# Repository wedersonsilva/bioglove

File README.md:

# Bioglove: Prototype of a bioinspired flexion transducer 
A project used in my undergraduate thesis [pt-br] 

# Abstract
Gloves embedded with sensors, also known as data gloves, allow interactions with virtual reality, robotics, control, internet of things, telemedicine, and so on. Essentially, such interaction occurs through the mapping of hands position as well as the flexion degree of the fingers for certain movements and actions within the environment in which the glove is submitted. The cost of the glove in many projects becomes prohibitive because of the technology chosen for such mapping. In the specific case of measuring the degree of flexion of the fingers — there are solutions based on fiber optics, conductive ink, resistive bending sensors and potentiometers. In order to reduce the cost of projects that require a data glove, was developed the BioGlove: a generic glove with low-cost embedded flexion sensors inspired by finger biomechanics. For the control and communication of the glove, a microcontroller board that has wide documentation and availability was used and a simplified protocol of communication and control was developed. The prototype developed was used for wireless control of an electronic car and its performance was compared with commercial solutions documented in the literature. The results showed that the BioGlove performs similarly to its competitors, especially in the flexion mapping and energy consumption requirements.

# Thesis
A .pdf version of the complete undergraduate thesis [pt-br] can be found .

# Note
This project was also known as Low Cost Flex Sensor (lcfs)

# Issues
Some archives are missing and they will be uploaded as soon as possible

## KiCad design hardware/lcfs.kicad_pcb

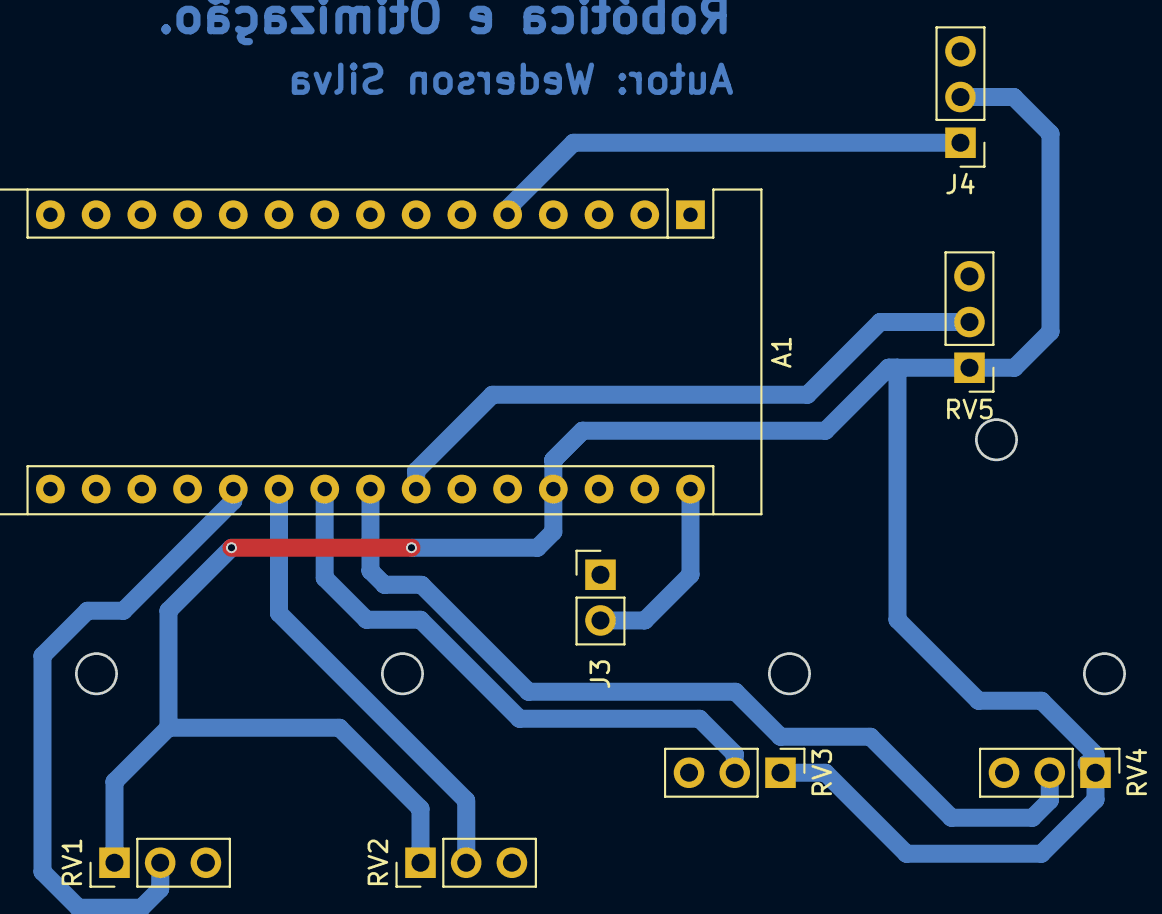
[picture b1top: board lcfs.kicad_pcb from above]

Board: 2 copper layers, 8 parts (0 on the bottom side), 9 nets.

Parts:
A1: Arduino_Nano
J3: Pin_1x2_Battery; Socket_Strip_Straight_1x02_Pitch2.54mm
J4: Pin_1x3_Transmissor; Socket_Strip_Straight_1x03_Pitch2.54mm
RV1: POT 1; Socket_Strip_Straight_1x03_Pitch2.54mm
RV2: POT 2; Socket_Strip_Straight_1x03_Pitch2.54mm
RV3: POT 3; Socket_Strip_Straight_1x03_Pitch2.54mm
RV4: POT 4; Socket_Strip_Straight_1x03_Pitch2.54mm
RV5: POT 5; Socket_Strip_Straight_1x03_Pitch2.54mm

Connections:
/5V: A1.27, J4.2, RV1.1, RV2.1, RV3.1, RV4.1, RV5.1
/7.2V: A1.30, J3.2
/DATA: A1.5, J4.1
/GND: A1.4, A1.29, J3.1, J4.3, RV1.3, RV2.3, RV3.3, RV4.3, RV5.3
unnamed: A1.20, RV1.2
unnamed: A1.21, RV2.2
unnamed: A1.22, RV3.2
unnamed: A1.23, RV4.2
unnamed: A1.24, RV5.2

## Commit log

2018-06-09 v.0.1.0 - Sending first archives
2018-06-09 v.0.1.1 - Sending first software test
2018-06-09 v0.1.2 - Ler cinco potenciomêtros e enviar ao Serial Monitor
2018-06-11 v0.1.3 - Incluir 2 softwares .ino para testar transmissão
2018-06-11 v0.1.4 - Segundo teste de transmissão de sinal concluído com sucesso
2018-06-13 v0.1.5 Remapeamento de valores lidos de 0-1023 para 1-8
2018-06-14 v0.1.6 Reorganiza e cria funcoes
2018-06-14 v0.1.7 Testa o envio de numeros variaveis
2018-06-14 v0.1.8 Inclui o projeto do Kicad
2018-06-15 v0.1.9 Inclui componentes no esquematico do Kicad
2018-06-16 v0.1.10 Esquemático finalizado e PCB iniciada
2018-06-19 v0.1.11 Inclui arquivos QCAD de desenho técnico
2018-06-19 v0.1.12 Posicionamento dos componentes na PCB
2018-06-19 v0.1.13 PCB organizada e não preenchida
2018-06-21 v0.1.14 PCB preenchida e inclusão da pasta pictures
2018-06-21 v0.1.15 Renomeia valores
2018-06-23 v0.1.16 Concatena e envia números variáveis
2018-06-23 Limpa (organiza) o código
2018-06-23 v0.1.18 Organiza e diminui o código ao mínimo
2018-06-24 v0.1.19 Coleta e envia valores variáveis para outro Arduino
2018-06-24 v0.1.20 <Bug> :bug: Apenas testa a mensagem de commit
2018-06-25 v0.1.21 :+1: Recebe, divide e transmite para 4 LEDs o código recebido
2018-06-30 v0.1.22 Envia e recebe 10 níveis de flexão
2018-07-01 v0.1.23 Inclui setup inicial do texto
2018-07-02 v0.2.2 Cria a estrutura básica do documento
2018-07-02 v0.2.3 Adiciona referências
2018-07-04 v0.2.4 Adiciona referências e o primeiro texto sobre Potenciômetro
2018-07-23 v0.2.5 Adiciona o SVG das mãos
2018-08-06 v0.2.6 Adiciona o SVG sobre potenciômetros
2018-08-06 v0.2.6 Adiciona a função de giro do potenciômetro
2018-08-07 v0.2.7 Compila todo o lcfs.tex após a última atualização
2018-08-07 v0.2.8 Adiciona texto ao trecho 'Movimentação dos Dedos'
2018-08-07 v0.2.9 Adiciona o movimento dos tendões na mão
2018-11-19 Adiciona fotos ao cap. 2 e texto ao cap. 3
2018-11-20 Adiciona desenhos ao cap. 3
2018-11-20 Inclui o desenho do receptor RF
2018-11-21 Inclui prints e fotos da PCB no Cap 3
2018-11-23 Conserta as referências e adapta o doc para o formato ABNT
2018-11-23 Deleta a pasta pictures e o arquivo .lcfs.tex.swp
2018-11-23 Compila o documento no formato ABNT
2018-11-24 Deleta e renomeia figuras
2018-11-25 Adiciona texto ao trecho 'Movimento Mecânico'
2018-11-26 Organiza e adiciona figuras no padrão ABNT ao cap. 3
2018-11-26 Reorganiza subcapítulos do cap. 3:w
2018-11-27 Adiciona a seção 'Montagem' ao Cap. 3
2018-11-27 Adiciona fotos melhores ao trabalho
2018-11-30 Adiciona correções baseadas no 1º feedback do orientador
2018-12-04 Adiciona primeiras correções e imagens baseadas no 2º feedback do orientador
2018-12-04 Adiciona mais correções baseadas no 2º feedback do orientador
2018-12-05 Adiciona textos e imagens sobre o protocolo de controle
2018-12-06 Adiciona a 1a versão após o 2º feedback do orientador
2018-12-06 Adiciona a 3a versão do Cap 3 após o 2º feedback do orientador
2018-12-13 Inclui novas referências para o Cap. 2
2018-12-15 Inclui ao Cap. 2 textos referenciados
2018-12-16 Adiciona o texto sobre microcontroladores
2018-12-18 Inclui a versão 3 do Cap. 2
2019-01-05 Inclui o início do Cap 4 e mais referências
2019-01-06 Inclui o trecho sobre baterias ao Cap. 4:w
2019-01-06 Conclui o trecho sobre baterias no Cap. 4
2019-01-07 Adiciona a versão 6 do TCC, com quase tudo mal finalizado
2019-02-18 Adiciona arquivos e testa funcionalidades do git
    As duas versões dos formulários (.doc e .pdf) usados na matrícula 2019.2 foram adicionadas ao
    projeto. Uma nova forma de commit, usando o editor nvim foi utilizada
    para escrever esse log.
2019-02-19 Inicia a correção baseado no 1º feedback de 2019
    Após receber o pdf com as marcações indicadas pelo orientador, foram
    iniciadas as correções baseadas nas marcações do último texto enviado em
    2018.
    Nesse primeiro momento, pequenos trechos foram excluídos ou alterados
    pontualmente baseado nas sugestões dadas.
2019-03-30 Conclui correções pontuais após 1º feedback 2019
    Baseado nesse 1º feedback, todas as sugestões de substituição,
    correção e exclusão de palavras e pequenos textos foram
    concluídas.
    Restando agora, correções que exigem uma escrita maior e mais
    elaborada.
2019-04-06 Corrige o trecho 1.1 baseado no Feedback 2019.1
2019-04-06 Corrige o trecho 1.4 baseado no Feedback 2019.1
    Feedback 2019.1 foi o primeiro feedback de 2019.
    O trecho 1.4 trata da organização do trabalho.
2019-04-08 Corrige o erro do nome da faculdade na capa
2019-05-09 Melhora o trecho 1.2 baseado no Feedback 2019.1
    Essas modificações visam melhorar o trecho do Estado
    da Arte, pois anteriormente praticamente apenas listava
    pesquisas de áreas relacionadas. Nesta versão foi
    adicionado mais detalhes sobre 2 pesquisas e 1 produto
    comercial relacionado ao trabalho realizado.
2019-05-14 Adiciona o pdf e citação no bibtex de uma referência
2019-05-20 Adiciona o trabalho de FLORES ao trecho 1.2
2019-05-25 Adiciona o trabalho de Collins ao trecho 1.2
2019-05-26 Reorganiza os parágrafos do trecho 1.2
2019-06-05 Organiza e adiciona informações ao trecho 2.1
    Mais parágrafos foram adicionados à esse trecho para que haja um
    melhor fluxo de infomações e uma explicação mais clara a
    respeito de como funcionam as aplicações com luvas sensorizadas
    em geral. Ao final um gancho para as demais subseções foi
    adicionado.
2019-06-06 Organiza e adiciona texto do trecho 2.2 ao 2.4
2019-06-06 Organiza e adiciona texto ao trecho 2.5
2019-06-07 Organiza e adiciona texto ao trecho 2.6
2019-06-08 Adiciona texto aos trecho 3.1 e 3.2.1
2019-06-08 Adiciona texto aos trecho 3.2.2 e 3.3
2019-06-08 Adiciona texto e organiza o trecho 3.3.1
2019-06-09 Cria e adiciona uma imagem ao trecho 3.3.1
2019-06-09 Organiza o trecho 3.3:w
2019-06-09 Adiciona imagem e texto a 3.4.1 e 3.4.2
    Nesse commit trechos dessas subseções são reorganizadas
    enquanto outros parágrafos foram adicionados. Além disso,
    mais uma imagem foi adicionada ao projeto no trecho 3.4.1.
2019-06-09 Adiciona texto e organiza o trecho 3.4.4
2019-06-10 Conclui o trecho 3.4 e subseções
2019-06-10 Atualiza os trechos 3.5.1 e 3.5.2
2019-06-11 Atualiza os trecho 3.5.3 com figura:w
2019-06-11 Conclui toda a seção 3.5
2019-06-11 Atualiza os trechos 4.1 e 4.2
2019-06-12 Conclui a atualização do TCC - v9
2019-06-12 Conclui a atualização do TCC v8
2019-06-15 Atualiza títulos, itálicos e siglas
2019-06-16 Atualiza agradecimentos e dedicatória
2019-06-17 Atualiza baseado no feedback 2019.2.1
2019-06-19 Atualiza v8 baseado no feedback 2019.2.3
2019-06-19 Atualiza v8 baseado no feedback 2019.2.4:w
2019-06-19 V9 baseado no feedback 2019.2
2019-06-24 v10 baseado no feedback 2019.3
2019-06-24 v10 atualiza baseado no feedback 2019.4
2019-06-24 Atualiza de acordo com o feedback 2019.4.2
2019-06-25 Versão enviada pra banca de defesa
2019-07-02 Adiciona poucos detalhes antes da defesa
2019-07-26 Adiciona correções da Prof. Joseane
2019-07-31 Adiciona correções sugeridas por Adalbery
2019-07-31 Adiciona as correções sugeridas pela banca
2019-07-31 Adiciona aprovação e catalográfica na pasta mas...
    Essas duas folhas ainda não foram adicionadas no
    documento final, portanto ainda é preciso resolver
    isso antes de entregar a versão final.
2019-08-01 Adiciona a versão final do documento
    Inclui as páginas de ficha catalográfica, folha
    de aprovação, além das correções sugeridas pela
    banca no dia da defesa. Esta foi a versão enviada
    por email à secretaria de Engenharia da Computação
    e Telecomicações.
2020-07-10 Add .gif da BioGlove
2020-07-10 Remove 'ufpatcc.cls'
2020-07-23 Add a link to the .pdf thesis on README
2022-12-13 remove old slide and add the correct one
2022-12-13 removing old thesis theme files
2022-12-13 remove some files and add a README.txt
2022-12-13 Modifica comentários para esclarecer melhor
